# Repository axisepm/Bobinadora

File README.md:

Bobinadora
==========

Proyecto de la bobinadora terminado

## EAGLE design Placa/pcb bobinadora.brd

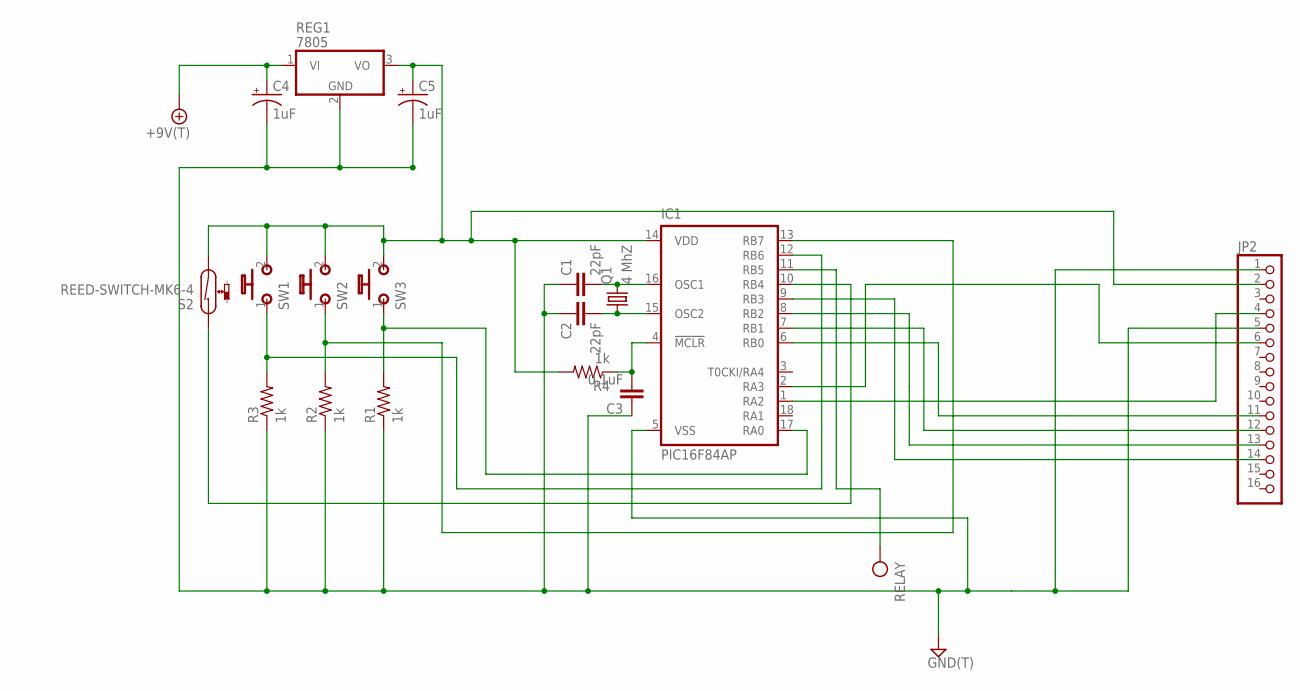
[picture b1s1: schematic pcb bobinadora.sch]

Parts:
+9V1: +9V(T); SQUARE
C1, C2: 22pF; 050X030_025
C3: 0,1uF; 050X030_025
C4, C5: 1uF; 050_020
GND2: GND(T); SQUARE
IC1: PIC16F84AP; DIL18
JP2: PINHD-1X16; 1X16
Q1: 4 MhZ; HC18U-V
R1, R2, R3, R4: 1k; R0207/4
REG1: 7805; TO92-
RELAY: OUT(T); SQUARE
S2: REED-SWITCH-MK6-4; MK6-4
SW1, SW2, SW3: MOMENTARY; SPST

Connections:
GND: C1.1, C2.1, C3.1, C4.-, C5.-, GND2.1, IC1.5 (VSS), R1.1, R2.1, R3.1, REG1.2 (GND)
unnamed: IC1.6 (RB0), JP2.11
unnamed: IC1.7 (RB1), JP2.12
unnamed: IC1.8 (RB2), JP2.13
unnamed: IC1.9 (RB3), JP2.14
unnamed: IC1.1 (RA2), JP2.4
unnamed: IC1.2 (RA3), JP2.6
unnamed: IC1.12 (RB6), R3.2, SW1.1
unnamed: IC1.13 (RB7), R2.2, SW2.1
unnamed: IC1.17 (RA0), R1.2, SW3.1
unnamed: C1.2, IC1.16 (OSC1), Q1.2
unnamed: IC1.10 (RB4), S2.1
unnamed: C2.2, IC1.15 (OSC2), Q1.1
unnamed: C3.2, IC1.4 (!MCLR), R4.1
unnamed: JP2.1, JP2.5
OUT: IC1.11 (RB5), RELAY.1
PWR: +9V1.1, C4.+, C5.+, IC1.14 (VDD), JP2.2, R4.2, REG1.1 (VI), REG1.3 (VO), S2.2, SW1.2 (S), SW2.2 (S), SW3.2 (S)

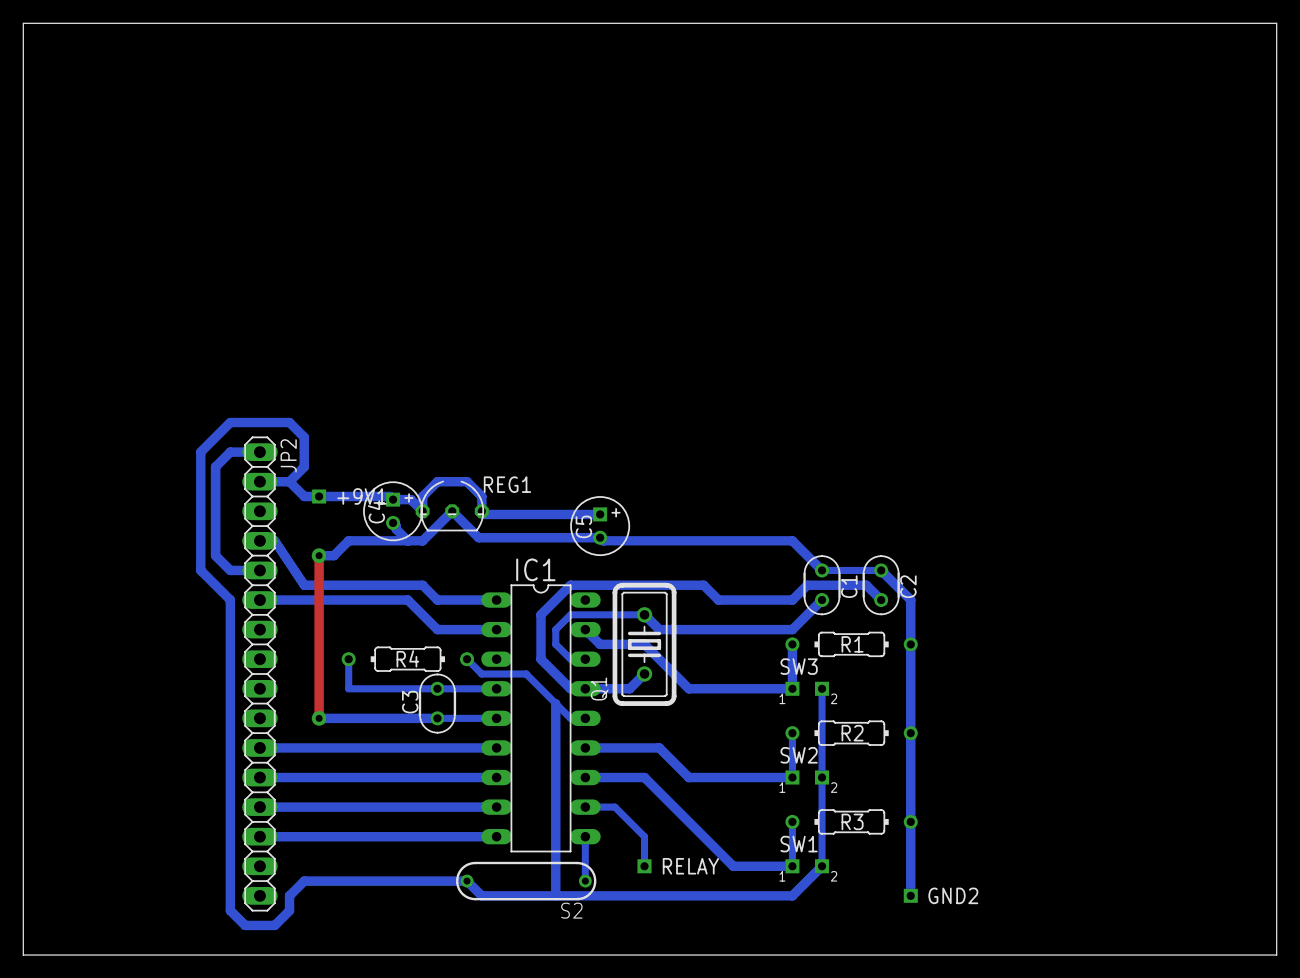
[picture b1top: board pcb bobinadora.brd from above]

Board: 2 copper layers, 107.6 x 80.0 mm, 20 parts (0 on the bottom side), 17 nets.

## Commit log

2013-02-10 proyecto
2013-02-19 Ultimo commit
    Producto Terminado
2013-03-18 cambios para acomodar los botones
2013-03-18 cambio x traza mas fina
2013-07-07 final
